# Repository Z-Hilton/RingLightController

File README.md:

# Ringlight Controller README

Welcome to the Ringlight Controller documentation! This guide will help you understand how the ringlight controller board works, even if you're not a programmer or electrical engineer. We'll break down the components, their functions, and the overall operation in a simple and organized manner.

## Table of Contents

1. **Introduction**
2. **Components**
3. **Power Supply**
4. **ESP32 Microcontroller**
5. **RGB LED Strip**
6. **Operation**

## 1. Introduction

The Ringlight Controller is a device designed to control a ringlight, which is often used for photography and video lighting. This controller is built around an ESP32 microcontroller and is capable of turning on and off the ringlight's LEDs in sync with a shutter signal.

###### Design Choices
This project from the start was meant to be done
* as fast as possible
* as simple as possible
* as robust as possible (i.e. can be easily improved upon later)

This means that there are potentially lots of optimizations that could be made, as I chose parts I am most familiar with and think that most people will find easy to use. Below I will provide a brief description of how the board works, piece by piece.

## 2. Components

#### 2.1 Mosfets (6)

- These are electronic switches that control the flow of electrical current. There are six of them on the board (circled in red below)

#### 2.2 Buck Converter

- This component steps down the input voltage from 24V to 5V. It provides power to both the ESP32 and the 3-pin RGB LED strip (not the 2-pin white leds, those need the full 24V). I refer to the entire blue PCB as one component - the buck converter. These can be bought for under a dollar at the BYU ECE shop (Northeast corner of the 4th floor of the Clyde building) or online. You can tune the output voltage using a small flat screwdriver. I have tuned them to output 5V, which can be checked using a handheld voltmeter.

#### 2.3 ESP32

The ESP32 is the heart of the controller. It performs the following tasks:

- **Detect Shutter Signal:** The ESP32 listens for a shutter signal coming from a 3.5mm headphone jack on the board. This signal tells the controller when to turn on the ringlight.

- **Control Mosfets:** When the shutter signal is detected, the ESP32 sends a signal to the Mosfets to turn them on. This allows the 24V power to flow to the white LED banks.

- **Control RGB LEDs** The ESP32 uses just one pin to control all 24 RGB LEDs of the ringlight. There are a couple of libraries you can use in the Arduino IDE to control them, with NEOpixel being arguably the easiest.
- For its dimensions and pinout, go [here.](https://docs.ai-thinker.com/en/esp32/boards/nodemcu_32s) Don't worry about anything else on that page, we program it using the Arduino IDE, which is much simpler than the process described by the manufacturer.

#### 2.4 JST connectors (6, 2-pins)

- Each of these go to a bank of 6 LEDs on the ringlight board that is mounted to a camera.

#### 2.5 JST connector (1, 3-pin)

- The three pins are ground, data, and power (5V). They go to the individually addressable RGB LEDs on the ringlight.

#### 2.6 3.5mm Jack

- Gets the signal from the camera

#### 2.7 Barrel Jack

- Gets power to the buck converter and ESP32

## 3. Supplying Power

The board expects an input of 24 Volts throught a **_center-positive_** DC barrel jack. You can check to see if your power source is center-positive by placing the red probe of a volt meter in the center of the plug and the black probe on the sleeve. If the number is positive you are all good. (This is important as there is no standard and center-negative is quite common too). The power supplies we are using for the photogrammetry rig are center-positive, so if you are a Makerspace employee reading this, no need to worry about this.
Again, here's how the power flows through the board:
- The 24V power goes into the board.
- A Buck Converter steps down the voltage to 5V.
- The 5V output powers both the ESP32 and the RGB LED strip.

## 6. Operation

Here's how the Ringlight Controller operates in simple terms:

1. **Power Supply:** Connect a 24V power source to the board.

2. **Shutter Signal:** Connect a device (e.g., a camera) to the 3.5mm headphone jack on the board. When you trigger the camera's shutter, it sends a signal to the board.

3. **ESP32 Activation:** The ESP32 detects the shutter signal and activates the Mosfets.

4. **Mosfet Activation:** The Mosfets turn on, allowing the 24V power to flow to the LED banks in the ringlight.

5. **Ringlight Illumination:** The ringlight's LEDs turn on, and we have lighting.

# WARNING!!!

- NEVER PLUG ANYTHING INTO THE MICROUSB IF THE BOARD IS BEING POWERED BY THE 24V BARREL JACK. IT WILL DESTROY THE ESP32 AND MAYBE THE COMPUTER PORT
- If/When you reprogram the board, make 100% sure that the 24V is unplugged. The board will power up from just the usb, but the ringlights won't light up, and that is fine. 

That's it! You should now understand each part of how the Ringlight Controller works.

## Comments on the code
- testLights.ino is a simple working version of the code that simply flashes the lights when it detects the shutter has opened. 
- RCP (which stands for Ringlight Control Protocol) is an implementation of a way to wirelessly change the settings (ie flash duration, flash color, etc.) of each of the boards without having to plug in to each board individually, as that proves VERY tedious. esp32's were chosen because of their WiFi capabilities. The sender code runs on a separate esp32 outside the rig, and the receiver code is meant to be ran on all the boards on the rig. Currently, none of the esp32s in the rig have this code on them because the RCP code was/is still under development.

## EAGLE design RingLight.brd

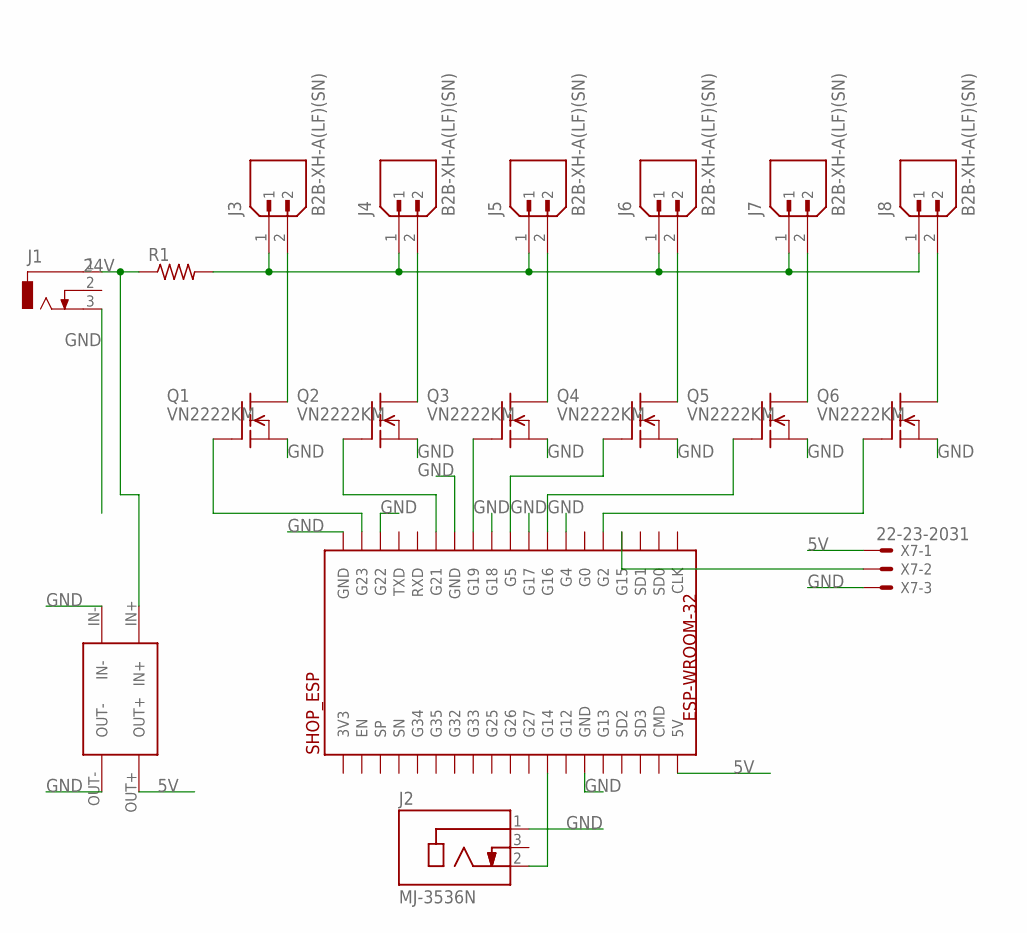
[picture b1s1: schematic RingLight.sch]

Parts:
J1: DCJ0303
J2: MJ-3536N; CUI_MJ-3536N
J3, J4, J5, J6, J7, J8: B2B-XH-A(LF)(SN); JST_B2B-XH-A(LF)(SN)
Q1, Q2, Q3, Q4, Q5, Q6: VN2222KM; TO237
R1: R-US_0204/7; 0204/7
U$2: BUCK-CONVERTER; LM2596DC-DC
U$4: SHOP_ESP; ESP32-WROOM-32
X7: 22-23-2031

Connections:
3V3: U$4.P$19 (3V3)
5V: U$2.OUT+, U$4.P$1 (5V), X7.1
24V: J1.1, R1.1, U$2.IN+
CMD: U$4.P$2 (CMD)
GND: J1.3, J2.1, Q1.3 (S), Q2.3 (S), Q3.3 (S), Q4.3 (S), Q5.3 (S), Q6.3 (S), U$2.IN-, U$2.OUT-, U$4.P$6 (GND), U$4.P$26 (G4), U$4.P$28 (G17), U$4.P$30 (G18), U$4.P$32 (GND), U$4.P$36 (G22), U$4.P$38 (GND), X7.3
IN: J3.1, J4.1, J5.1, J6.1, J7.1, J8.1, R1.2
unnamed: J3.2, Q1.1 (D)
unnamed: J4.2, Q2.1 (D)
unnamed: J5.2, Q3.1 (D)
unnamed: J6.2, Q4.1 (D)
unnamed: J7.2, Q5.1 (D)
unnamed: Q1.2 (G), U$4.P$37 (G23)
unnamed: U$4.P$23 (G15), X7.2
unnamed: Q2.2 (G), U$4.P$33 (G21)
unnamed: Q3.2 (G), U$4.P$31 (G19)
unnamed: Q4.2 (G), U$4.P$29 (G5)
unnamed: Q5.2 (G), U$4.P$27 (G16)
unnamed: Q6.2 (G), U$4.P$24 (G2)
unnamed: J2.2, U$4.P$8 (G14)
unnamed: J8.2, Q6.1 (D)

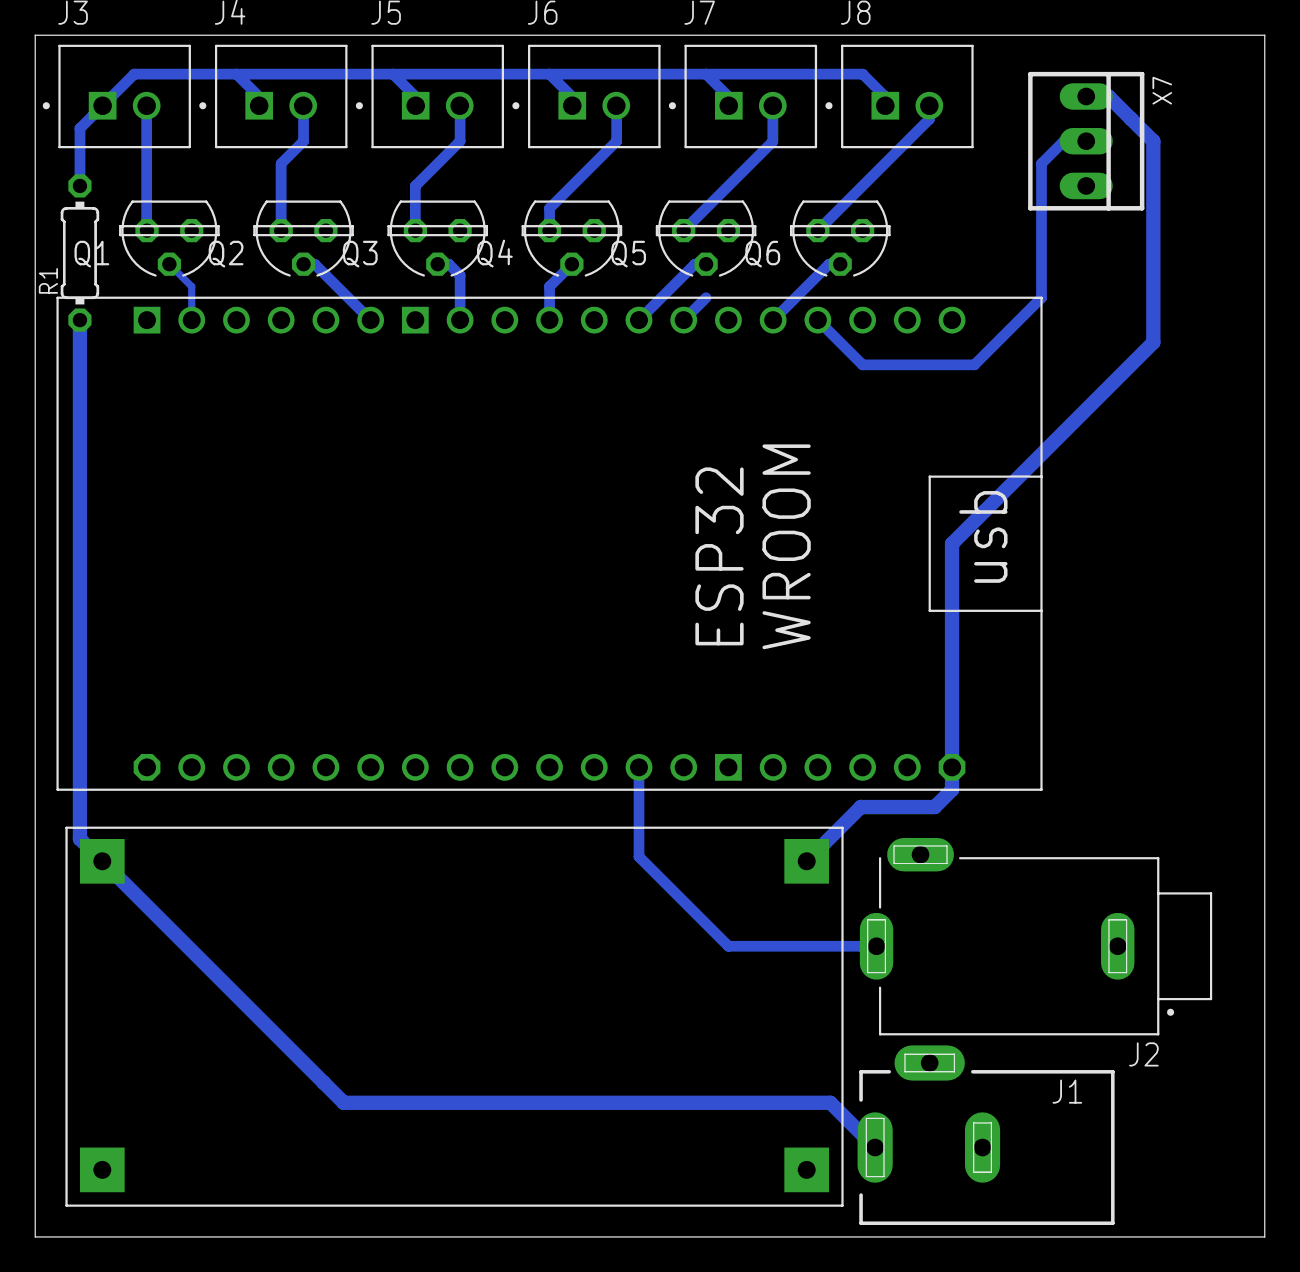
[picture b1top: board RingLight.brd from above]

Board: 2 copper layers, 69.8 x 68.2 mm, 18 parts (0 on the bottom side), 18 nets.

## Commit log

2023-10-05 v2 beta board
2023-10-05 Created a folder
2023-10-05 Moved
2023-10-05 moved to folder
2023-10-05 Create temp
2024-08-01 Updated testLights.ino
    Updated the pins to work with the new NodeMCU esp32 and corresponding PCB. The new code has the lights always dimly on to help the cameras focus. The main flash is the same as before.
2024-12-03 Added esp32 documentation
    This is the datasheet that has the pinout for the specific esp32's I used in the ringlights.
2025-01-04 added pictures with highlighting
2025-01-04 Update README.md
    Added highlighted images, changed description of buck converter, linked to the pinout of the esp32
